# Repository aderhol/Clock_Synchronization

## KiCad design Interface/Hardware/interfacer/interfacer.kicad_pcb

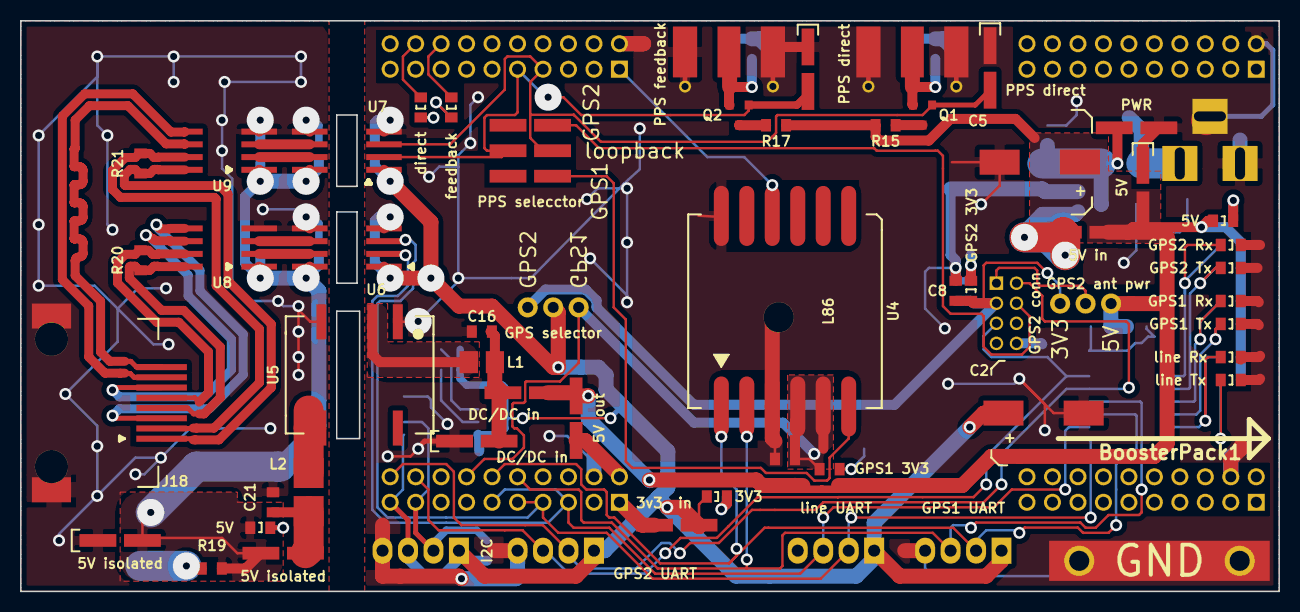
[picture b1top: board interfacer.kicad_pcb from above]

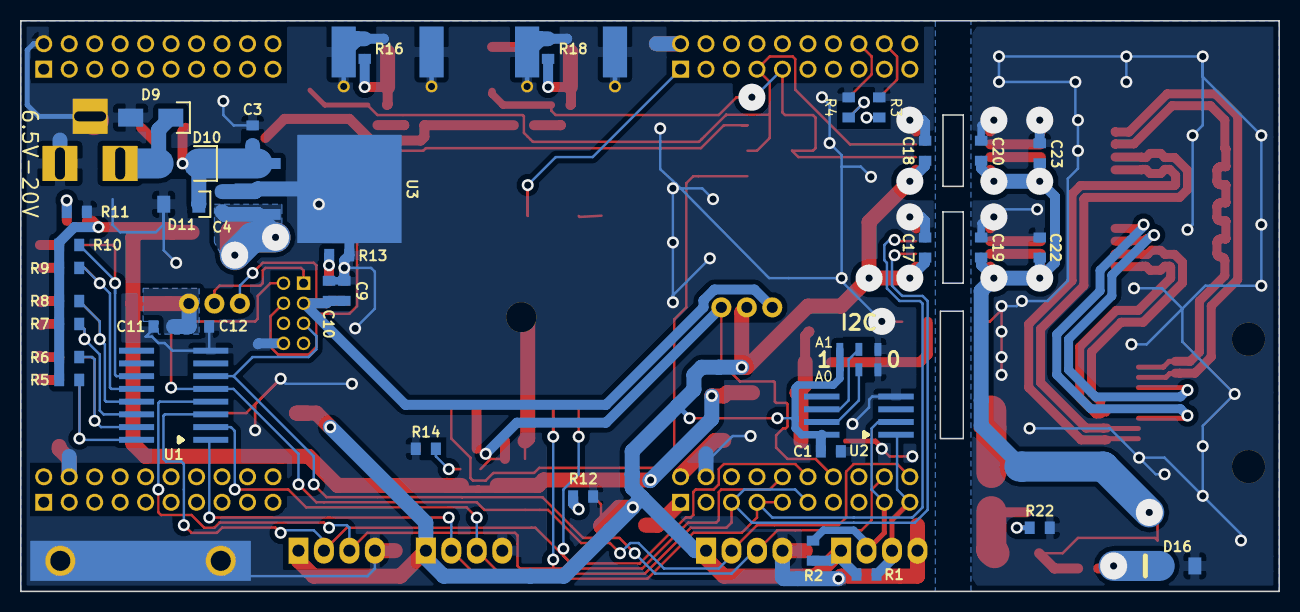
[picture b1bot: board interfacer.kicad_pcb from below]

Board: 2 copper layers, 125.5 x 56.9 mm, 103 parts (43 on the bottom side), 64 nets.

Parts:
C1, C9, C12, C13, C17, C18, C19, C20, C22, C23: 0.1u; 0805_2012
C2, C5: 1000u; CP_Elec_10x10
C3: 0.47u; 0805_2012
C4: 22u; 0805_2012
C8, C11, C14: 1u; 0805_2012
C10: 0.01u; 0805_2012
C15: 10u; 0805_2012
C16: 4.7u; 0805_2012
C21: 2.2u; 0805_2012
D1: direct; 0805_2012
D2: feedback; 0805_2012
D3: line Tx; 0805_2012
D4: line Rx; 0805_2012
D5: GPS1 Tx; 0805_2012
D6: GPS1 Rx; 0805_2012
D7: GPS2 Tx; 0805_2012
D8: GPS2 Rx; 0805_2012
D9, D10: 1A - 20V; D_SMA
D11: 24V; D_MiniMELF
D12, D17: 5V; 0805_2012
D13: 3V3; 0805_2012
D14: GPS2 3V3; 0805_2012
D15: GPS1 3V3; 0805_2012
D16: 5V1; D_MiniMELF
J1: I2C; Molex_KK-6410-04_04x2.54mm_Straight
J2: line UART; Molex_KK-6410-04_04x2.54mm_Straight
J3: GPS2 UART; Molex_KK-6410-04_04x2.54mm_Straight
J4: GPS1 UART; Molex_KK-6410-04_04x2.54mm_Straight
J5: PPS direct; 2P_2.54_SMD
J6: PPS selecctor; Pin_Header_Straight_2x03_Pitch2.54mm_SMD_clockwise-numbering
J7: PPS feedback; 2P_2.54_SMD
J8: left bottom conn; Pin_Header_Straight_2x10_Pitch2.54mm_column-numbering
J9: right bottom conn; Pin_Header_Straight_2x10_Pitch2.54mm_column-numbering
J10: 5VDC barrel jack; BARREL_JACK
J11: PWR; 2P_2.54_SMD
J12: 5V; 2P_2.54_SMD
J13: GPS2 conn; Pin_Header_Straight_2x04_Pitch2.00mm_column-numbering
J14: PPS direct; Molex_SMA_Jack_Edge_Mount
J15: PPS feedback; Molex_SMA_Jack_Edge_Mount
J16: DC/DC in; 2P_2.54_SMD
J17: 5V isolated; 2P_2.54_SMD
J18: RJ45; 8P8C_SMD
J19: left top conn; Pin_Header_Straight_2x10_Pitch2.54mm_column-numbering
J20: right top conn; Pin_Header_Straight_2x10_Pitch2.54mm_column-numbering
JP1: GPS selector; 3P_2.54_jumper
JP2: 5V out; 2P_2.54_SMD
JP3: 3v3 in; 2P_2.54_SMD
JP4: A0; 0_Ohm_jumper
JP5: A1; 0_Ohm_jumper
JP6: 5V in; 2P_2.54_SMD
JP7: GPS2 ant pwr; 3P_2.54_jumper
JP8: 5V isolated; 2P_2.54_SMD
JP9: DC/DC in; 2P_2.54_SMD
L1: 4.7u; L_Taiyo-Yuden_NR-24xx_HandSoldering
L2: 10u; Bourns_SDR0302_Series
Q1, Q2: BSV52LT1G; SOT-23
R1, R2, R6, R8, R10, R11, R22: 2k; 0805_2012
R3, R4: 390; 0805_2012
R5, R7, R9: 10k; 0805_2012
R12, R13, R14: 1k5; 0805_2012
R15, R17: 50; 0805_2012
R16, R18: inf; 0805_2012
R19: 0; 0805_2012
R20, R21: 100; 0805_2012
TP1: GND; GND_probe
U1: ULN2003A; SOIC-16
U2: LM92; SOIC-8
U3: LM2940S-5.0; TO-263-3_TabPinMiddle
U4: L86
U5: NXJ1S0505MC; muRata_NXJ1-Series
U6, U7: ISO7421E; SOIC-8
U8, U9: SN65LBC179A; SOIC-8

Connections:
+3V3: C1.1, C2.1, C17.1, C18.1, D13.2, J1.1, J2.1, J3.1, J4.1, JP1.2, JP3.2, JP4.3, JP5.3, R1.1, R2.1, U2.8, U6.1, U7.1
+5V: C5.1, C11.1, C12.1, D12.2, J12.2, JP2.2, JP6.2, JP7.3, JP9.1, R5.1, R6.1, R7.1, R8.1, R9.1, R10.1, R15.2, R17.2
+5VP: C19.1, C20.1, C22.1, C23.1, D17.2, J17.1, JP8.2, R19.1, U6.8, U7.8, U8.1, U9.1
/50-Ohm PPS/PPS_direct: J5.2, J6.2, J8.4, Q1.1, U7.3
/50-Ohm PPS/PPS_feedback: J6.5, J7.2, J8.5, Q2.1, U7.2
/GPS1/3V3: C13.1, C14.1, C15.1, D15.2, J9.17, JP1.1, U4.4, U4.5
/GPS1/PPS: J6.1, U4.6
/GPS2/3V3: C8.1, C9.1, C10.1, D14.2, J13.2, JP1.3, JP7.1
/GPS2/ANT_PWR: J13.1, JP7.2
/GPS2/PPS: J6.3, J13.6
/RS-422 interface/PPS_in+: J18.1, R21.1, U9.8
/RS-422 interface/PPS_in-: J18.2, R21.2, U9.7
/RS-422 interface/PPS_out+: J18.7, U9.5
/RS-422 interface/PPS_out-: J18.8, U9.6
/RS-422 interface/Rx+: J18.4, R20.1, U8.8
/RS-422 interface/Rx-: J18.5, R20.2, U8.7
/RS-422 interface/Tx+: J18.3, U8.5
/RS-422 interface/Tx-: J18.6, U8.6
/debugging LEDs/LED_PPS_direct: D1.2, J8.19
/debugging LEDs/LED_PPS_feedback: D2.2, J8.18
/debugging LEDs/LED_Rx_line: J2.3, J9.3, J9.6, U1.2, U6.2
/debugging LEDs/LED_Tx_line: J2.2, J9.4, J9.5, U1.1, U6.3
/main connector/3V3_in: J9.1, JP3.1
/main connector/5V_out: J9.11, JP2.1
/main connector/GPS_1_Rx: J4.3, J9.15, U1.4, U4.2
/main connector/GPS_1_Tx: J4.2, J9.16, U1.3, U4.1
/main connector/GPS_1_reset: J8.1, U4.10
/main connector/GPS_2_Rx: J3.3, J9.19, J13.3, U1.6
/main connector/GPS_2_Tx: J3.2, J9.20, J13.5, U1.5
/main connector/I2C_SCL: J1.2, J9.9, R2.2, U2.2
/main connector/I2C_SDA: J1.3, J9.10, R1.2, U2.1
GND: C1.2, C2.2, C3.2, C4.2, C5.2, C8.2, C9.2, C10.2, C11.2, C12.2, C13.2, C14.2, C15.2, C16.2, C17.2, C18.2, D3.1, D4.1, D5.1, D6.1, D7.1, D8.1, D9.2, D11.2, J1.4, J2.4, J3.4, J4.4, J5.1, J7.1, J8.11, J9.12, J10.2, J10.3, J11.1, J12.1, J13.8, J14.2, J15.2, J16.2, J19.11, J20.12, JP4.1, JP5.1, R3.2, R4.2, R11.2, R12.2, R13.2, R14.2, R16.2, R18.2, TP1.1, U1.8, U2.4, U3.1, U4.3, U4.12, U5.1, U6.4, U7.4
GNDPWR: C19.2, C20.2, C21.2, C22.2, C23.2, D16.2, J17.2, J18.9, R22.2, U5.7, U6.5, U7.5, U8.4, U9.4
unnamed: C3.1, D10.1, D11.1, J11.2, U3.3
unnamed: C4.1, JP6.1, U3.2
unnamed: C16.1, J16.1, JP9.2, L1.2
unnamed: C21.1, JP8.1, L2.1
unnamed: D1.1, R3.1
unnamed: D2.1, R4.1
unnamed: D3.2, R5.2, U1.16
unnamed: D4.2, R6.2, U1.15
unnamed: D5.2, R7.2, U1.14
unnamed: D6.2, R8.2, U1.13
unnamed: D7.2, R9.2, U1.12
unnamed: D8.2, R10.2, U1.11
unnamed: D9.1, D10.2, J10.1
unnamed: D12.1, R11.1
unnamed: D13.1, R12.1
unnamed: D14.1, R13.1
unnamed: D15.1, R14.1
unnamed: D16.1, R19.2
unnamed: D17.1, R22.1
unnamed: J14.1, Q1.2, R16.1
unnamed: J15.1, Q2.2, R18.1
unnamed: JP4.2, U2.7
unnamed: JP5.2, U2.6
unnamed: L1.1, U5.3
unnamed: L2.2, U5.8
unnamed: Q1.3, R15.1
unnamed: Q2.3, R17.1
unnamed: U6.6, U8.3
unnamed: U6.7, U8.2
unnamed: U7.6, U9.3
unnamed: U7.7, U9.2

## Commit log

2017-10-25 initial
2017-10-27 silkscreen and solder mask finalization wiring touch-up
2017-10-29 8P8C, GPS1 gnd pin fix
2017-11-14 assembly record
2017-11-15 card #1 assembled
2017-11-15 resistor change for green LEDs
2017-11-15 antenna power touch-up & green LED resistor value change
2017-11-15 added pin names to the main connector
2017-11-16 temperature sensor (I2C)
2017-11-16 line UART out
2017-11-17 card#2 partially assembled
2017-11-19 PPS delay measurement data
2017-11-19 latency measurement
2017-11-20 $GPINFO
2017-11-20 50 Ohm driver latency measurements
2017-11-21 command-over-line, views, and PPS LEDs
2017-11-21 reset & GPS1 inital config (115200 baud, timing product)
2017-11-21 Revert "reset & GPS1 inital config (115200 baud, timing product)"
    This reverts commit ed776d911817a95cc33cef9cfc96954527a65ba9.
2017-11-21 MIT 03.104-03.105
2017-11-21 GPS module, PPS feedback 50 ohm drive, molex connectors
2017-12-22 UART buffer size increase
2017-12-22 card#2 PPS feedback 50 Ohm driver latency measurement
2018-01-16 Resolution SMTx datasheets added
2018-02-01 GPS_2 selectable
2018-02-01 temperature dependence measurements
2018-02-01 117cm round-trip measurement
2018-02-05 rolling average
2018-02-05 housekeeping
2018-02-05 tidy up commands
2018-02-11 PPS measurement in the departmental network
2018-03-05 clock over line
2018-03-05 bridge PC-line and line-GPS2
2018-03-05 GPS2 is set as default
2018-03-05 Trimble Studio
2018-03-09 persistent config, additional feedbacks for commands , bridge bug fix
2018-03-14 Measurement GUI
2018-03-21 TSIP
2018-03-21 TSIP bug fix
2019-09-11 $GPINF checksum fix
